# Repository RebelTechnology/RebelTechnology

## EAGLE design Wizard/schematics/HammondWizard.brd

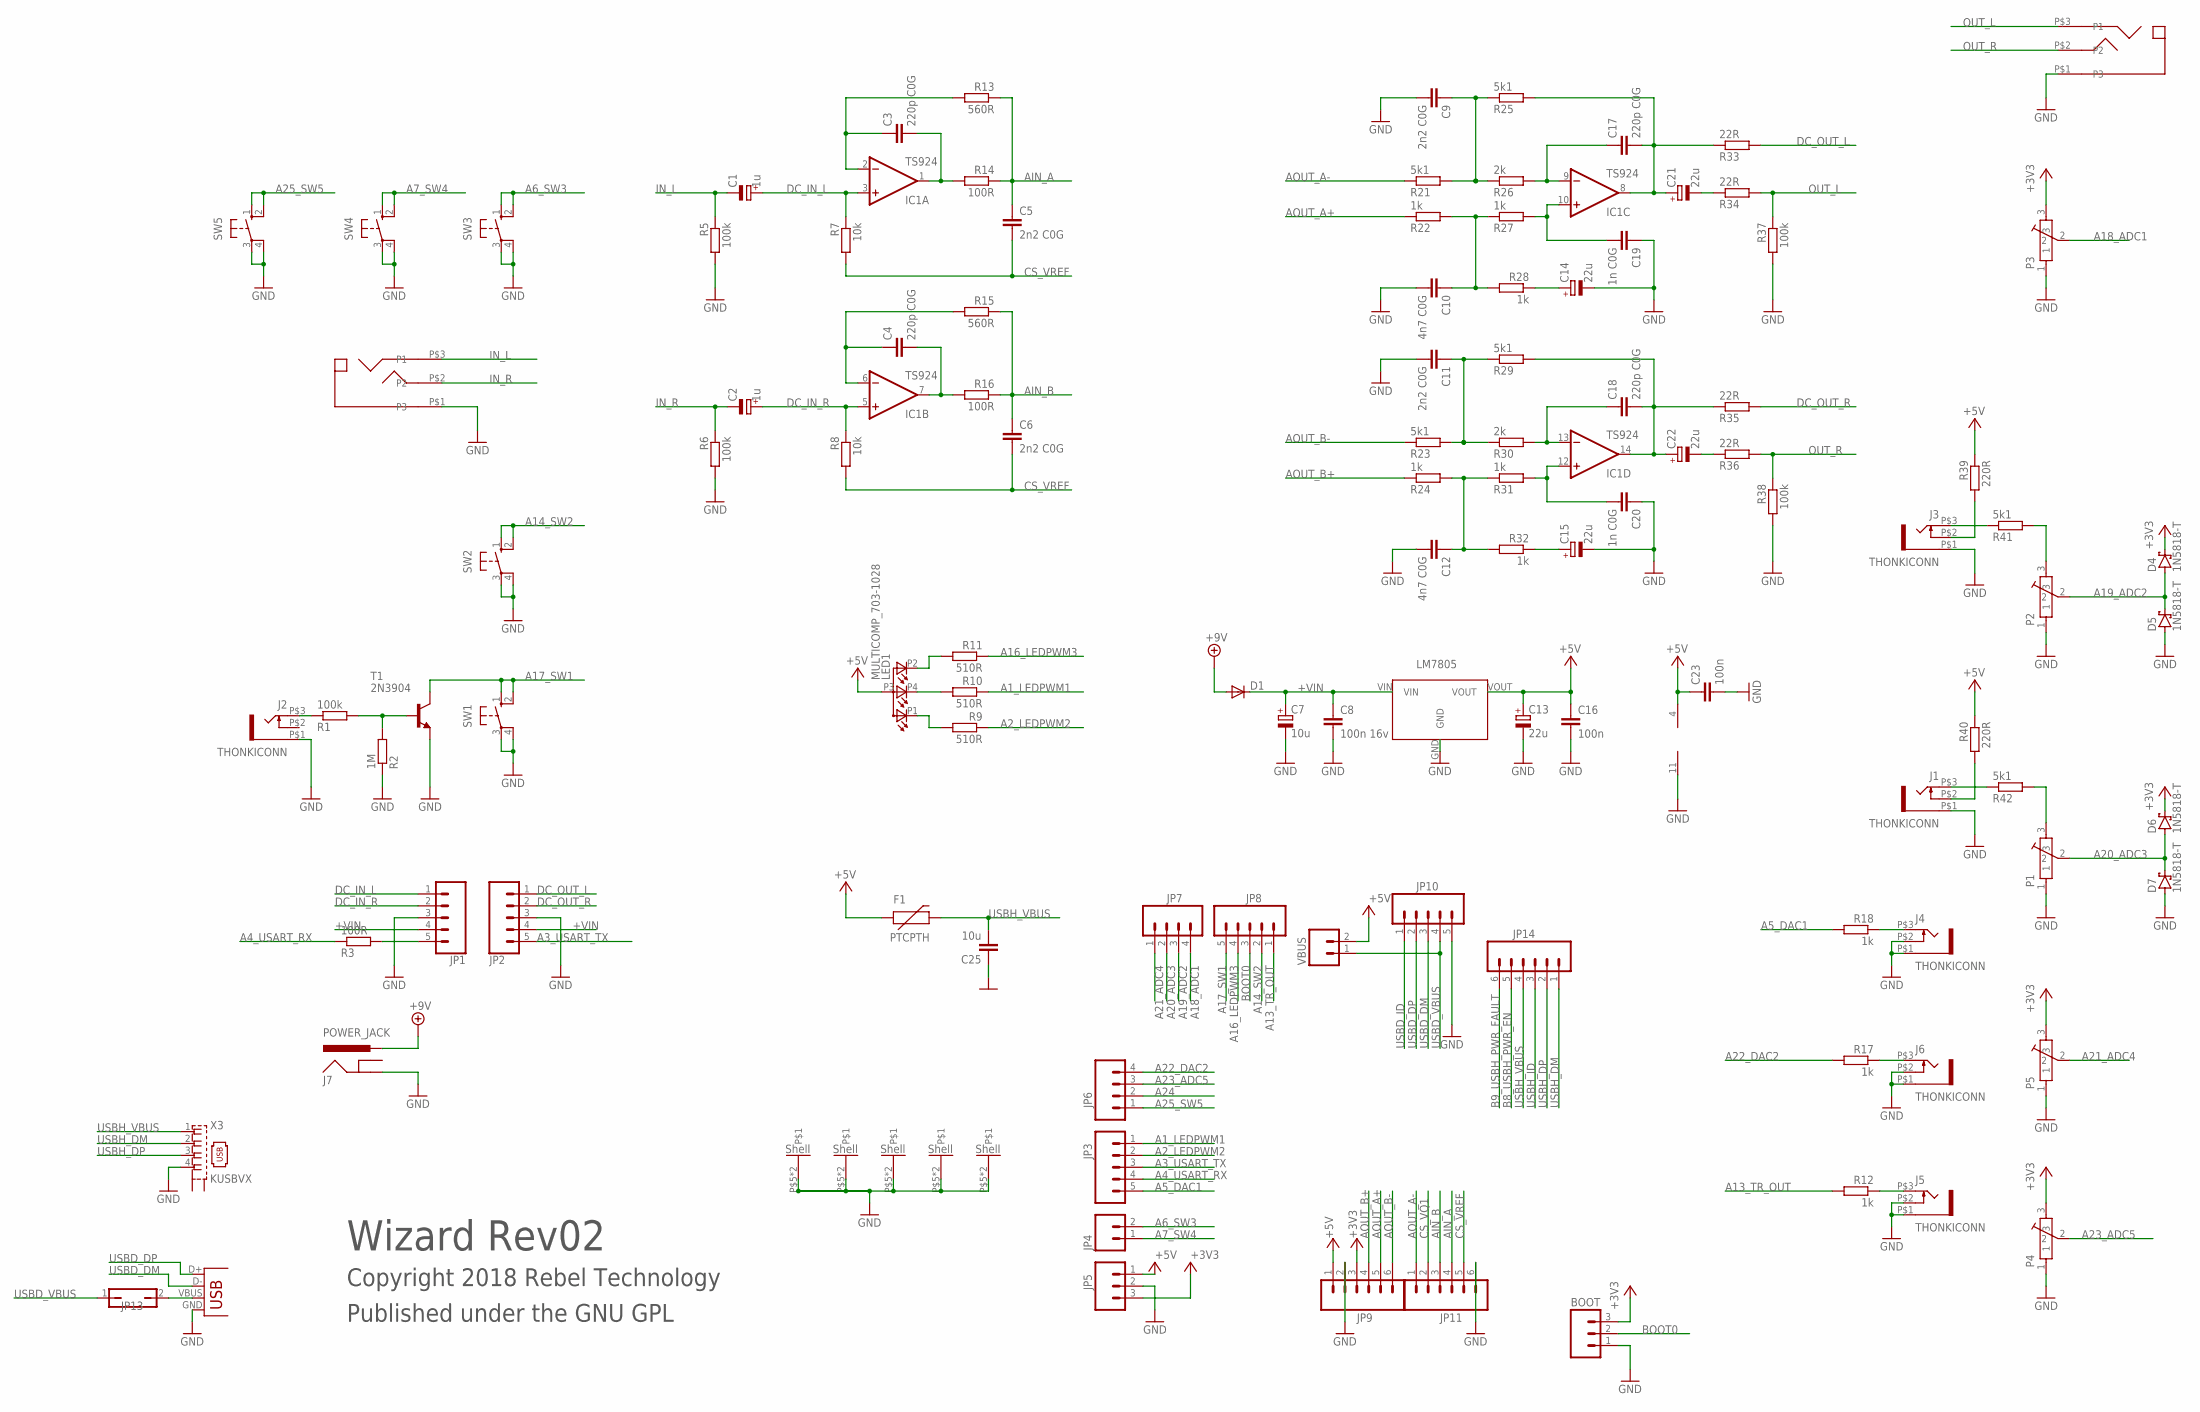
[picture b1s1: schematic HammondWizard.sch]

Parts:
BOOT: M03PTH; 1X03
C1, C2: 1u; E5-6
C3, C4, C17, C18: 220p C0G; C050-024X044
C5, C6, C9, C11: 2n2 C0G; C050-024X044
C7: 10u; E5-6
C8: 100n 16v; C050-024X044
C10, C12: 4n7 C0G; C050-024X044
C13, C14, C15, C21, C22: 22u; E5-6
C16, C23: 100n; C050-024X044
C19, C20: 1n C0G; C050-024X044
C25: 10u; C050-024X044
D1: DIODE1N4001; DIODE-1N4001
D4, D5, D6, D7: 1N5818-T; DO41-7.6
F1: PTCPTH; PTC
IC1: TS924; DIL14
J1, J2, J3, J4, J5, J6: THONKICONN
J7: POWER_JACK; DC_JACK_SLOT
JP1, JP2: CONN_05JST-VERT; JST-5-PTH-VERT
JP3, JP8, JP10: M05PTH; 1X05
JP4: M02PTH; 1X02
JP5: M03PTH; 1X03
JP6, JP7: M04PTH; 1X04
JP9, JP11, JP14: M06SIP; 1X06
JP13: JP1Q; JP1
LED1: MULTICOMP_703-1028; RGB-LED-703-1028
P1, P2, P3, P4, P5: POT-ALPS-RK09L1140
R1, R5, R6, R37, R38: 100k; 0204/7
R2: 1M; 0204/7
R3, R14, R16: 100R; 0204/7
R7, R8: 10k; 0204/7
R9, R10, R11: 510R; 0204/7
R12, R17, R18, R22, R24, R27, R28, R31, R32: 1k; 0204/7
R13, R15: 560R; 0204/7
R21, R23, R25, R29, R41, R42: 5k1; 0204/7
R26, R30: 2k; 0204/7
R33, R34, R35, R36: 22R; 0204/7
R39, R40: 220R; 0204/7
SW1, SW2, SW3, SW4, SW5: 10-XX; B3F-10XX
T1: 2N3904; TO92
U2: LM7805; REG_S9V11F5
U$4, U$5: THONKICONN_STEREO
VBUS: M02PTH; 1X02
X3: KUSBVX
X5: USBPTH-VERTICAL; USB-B-PTH-VERTICAL

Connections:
+3V3: BOOT.3, D4.C, D6.C, JP5.3, JP9.3, P3.3, P4.3, P5.3
+5V: C13.+, C16.1, C23.1, F1.P$1 (1), IC1.4 (V+), JP5.1, JP9.1, LED1.P3 (A), R39.1, R40.1, U2.VOUT, VBUS.2
+9V: D1.A, J7.PWR
+VIN: C7.+, C8.1, D1.C, JP1.4, JP2.4, U2.VIN
A1_LEDPWM1: JP3.1, R10.1
A2_LEDPWM2: JP3.2, R9.1
A3_USART_TX: JP2.5, JP3.3
A4_USART_RX: JP3.4, R3.1
A5_DAC1: JP3.5, R18.2
A6_SW3: JP4.2, SW3.1 (S), SW3.2 (S1)
A7_SW4: JP4.1, SW4.1 (S), SW4.2 (S1)
A13_TR_OUT: JP8.1, R12.2
A14_SW2: JP8.2, SW2.1 (S), SW2.2 (S1)
A16_LEDPWM3: JP8.4, R11.1
A17_SW1: JP8.5, SW1.1 (S), SW1.2 (S1), T1.1 (C)
A18_ADC1: JP7.4, P3.2
A19_ADC2: D4.A, D5.C, JP7.3, P2.2
A20_ADC3: D6.A, D7.C, JP7.2, P1.2
A21_ADC4: JP7.1, P5.2
A22_DAC2: JP6.4, R17.2
A23_ADC5: JP6.3, P4.2
A24: JP6.2
A25_SW5: JP6.1, SW5.1 (S), SW5.2 (S1)
AIN_A: C5.1, JP11.4, R13.1, R14.1
AIN_B: C6.1, JP11.3, R15.1, R16.1
AOUT_A+: JP9.5, R22.1
AOUT_A-: JP11.1, R21.1
AOUT_B+: JP9.4, R24.1
AOUT_B-: JP9.6, R23.1
B8_USBH_PWR_EN: JP14.5
B9_USBH_PWR_FAULT: JP14.6
BOOT0: BOOT.2, JP8.3
CS_VQ1: JP11.2
CS_VREF: C5.2, C6.2, JP11.5, R7.2, R8.2
DC_IN_L: C1.+, IC1.3 (+IN), JP1.1, R7.1
DC_IN_R: C2.+, IC1.5 (+IN), JP1.2, R8.1
DC_OUT_L: JP2.1, R33.2
DC_OUT_R: JP2.2, R35.2
GND: BOOT.1, C7.-, C8.2, C9.2, C10.2, C11.2, C12.2, C13.-, C14.-, C15.-, C16.2, C19.1, C20.1, C23.2, C25.1, D5.A, D7.A, IC1.11 (V-), J1.P$1 (5), J2.P$1 (5), J3.P$1 (5), J4.P$1 (5), J4.P$2 (4), J5.P$1 (5), J5.P$2 (4), J6.P$1 (5), J6.P$2 (4), J7.GND, JP1.3, JP2.3, JP5.2, JP9.2, JP10.5, JP11.6, P1.1, P1.P$5, P1.P$6, P2.1, P2.P$5, P2.P$6, P3.1, P3.P$5, P3.P$6, P4.1, P4.P$5, P4.P$6, P5.1, P5.P$5, P5.P$6, R2.1, R5.2, R6.2, R37.2, R38.2, SW1.3, SW1.4 (P1), SW2.3, SW2.4 (P1), SW3.3, SW3.4 (P1), SW4.3, SW4.4 (P1), SW5.3, SW5.4 (P1), T1.3 (E), U2.GND, U$4.P$1 (P3), U$5.P$1 (P3), X3.4, X5.GND
IN_L: C1.-, R5.1, U$4.P$3 (P1)
IN_R: C2.-, R6.1, U$4.P$2 (P2)
unnamed: JP1.5, R3.2
unnamed: J1.P$2 (4), R40.2
unnamed: C3.1, IC1.2 (-IN), R13.2
unnamed: C4.2, IC1.7 (OUT), R16.2
unnamed: C4.1, IC1.6 (-IN), R15.2
unnamed: C3.2, IC1.1 (OUT), R14.2
unnamed: C17.1, IC1.9 (-IN), R26.2
unnamed: C15.+, R32.1
unnamed: C21.-, R34.1
unnamed: C14.+, R28.1
unnamed: C19.2, IC1.10 (+IN), R27.2
unnamed: C18.2, C22.+, IC1.14 (OUT), R29.2, R35.1
unnamed: C22.-, R36.1
unnamed: LED1.P2 (CGREEN), R11.2
unnamed: C10.1, R22.2, R27.1, R28.2
unnamed: LED1.P1 (CRED), R9.2
unnamed: LED1.P4 (CBLUE), R10.2
unnamed: JP13.2, X5.VBUS
unnamed: J5.P$3 (3), R12.1
unnamed: J6.P$3 (3), R17.1
unnamed: J4.P$3 (3), R18.1
unnamed: J2.P$3 (3), R1.1
unnamed: J3.P$2 (4), R39.2
unnamed: C11.1, R23.2, R29.1, R30.1
unnamed: P2.3, R41.2
unnamed: C18.1, IC1.13 (-IN), R30.2
unnamed: J3.P$3 (3), R41.1
unnamed: C20.2, IC1.12 (+IN), R31.2
unnamed: P1.3, R42.2
unnamed: C12.1, R24.2, R31.1, R32.2
unnamed: J1.P$3 (3), R42.1
unnamed: R1.2, R2.2, T1.2 (B)
unnamed: C17.2, C21.+, IC1.8 (OUT), R25.2, R33.1
unnamed: C9.1, R21.2, R25.1, R26.1
OUT_L: R34.2, R37.1, U$5.P$3 (P1)
OUT_R: R36.2, R38.1, U$5.P$2 (P2)
USBD_DM: JP10.3, X5.D-
USBD_DP: JP10.2, X5.D+
USBD_ID: JP10.1
USBD_VBUS: JP10.4, JP13.1, VBUS.1
USBH_DM: JP14.1, X3.2
USBH_DP: JP14.2, X3.3
USBH_ID: JP14.3
USBH_VBUS: C25.2, F1.P$2 (2), JP14.4, X3.1

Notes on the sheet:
Wizard Rev02
Copyright 2018 Rebel Technology
Published under the GNU GPL

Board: 2 copper layers, 115 parts (75 on the bottom side), 79 nets, no tracks yet.

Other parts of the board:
U$1, U$2: 2,8
U$6, U$7, U$8, U$9: 3,6

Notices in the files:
parts and their libraries:
SparkFun: Licensing: CC v3.0 Share-Alike You are welcome to use this library for commercial purposes.
SparkFun-Connectors: Licensing: Creative Commons ShareAlike 4.0 International - https://creativecommons.org/licenses/by-sa/4.0
